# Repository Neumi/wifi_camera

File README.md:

# wifi_camera

### A camera that can see WiFi signals. Just the sensor unit. Currently planned for 8x8=64 pixels.

3D capture of a wifi signal in a 20x20x20 cm grid.

## What it does
The sensor array captures RSSI values from near by WiFi networks and sends the collected pixel data to a master that processes and visualizes the captured data. The goal is to build a sensor, that makes WiFi signal visible in more or less real time.

## Why? 
WiFi signals are invisible to humans. I think it would be fun to make them visible and play around with it. Projects I have in mind unsing the sensor array: real time analysis of antennas and obstacles..., real time object/person detection/tracking by reading WiFi shadows and reflections, using the standing wave to 'surf' it to get position data back for i.e. robots.

## How?
Before this, I built a rig to scan and visualize WiFi signal propagation in 3D 

https://hackaday.com/2021/11/22/visualizing-wifi-with-a-converted-3d-printer/

https://github.com/Neumi/3D_wifi_scanner

This got me interested in building a real time, sensor array to take a whole frame at once without having to scan a slice one position after another.

To capture a whole slice at once, I built this array unsing four PCBs with 4x4 ESP8266 sensor nodes connected via i2c where every pixel is an i2c slave and a master that asks the pixels one by one for the captured values.

I'm currently waiting fore more ESP8266s to arrive.

## Results
The results look pretty granular currently, as I only used 4x4 pixels, which is a bit low. When more ESPs arrive, I will take more images.

16 Pixels, x-axis is time, Y axis is RSSI with an offset between each pixel for visibility.

16 Pixels with correct orientation in a 2D plot. 

## Video of 4x4 test grid:

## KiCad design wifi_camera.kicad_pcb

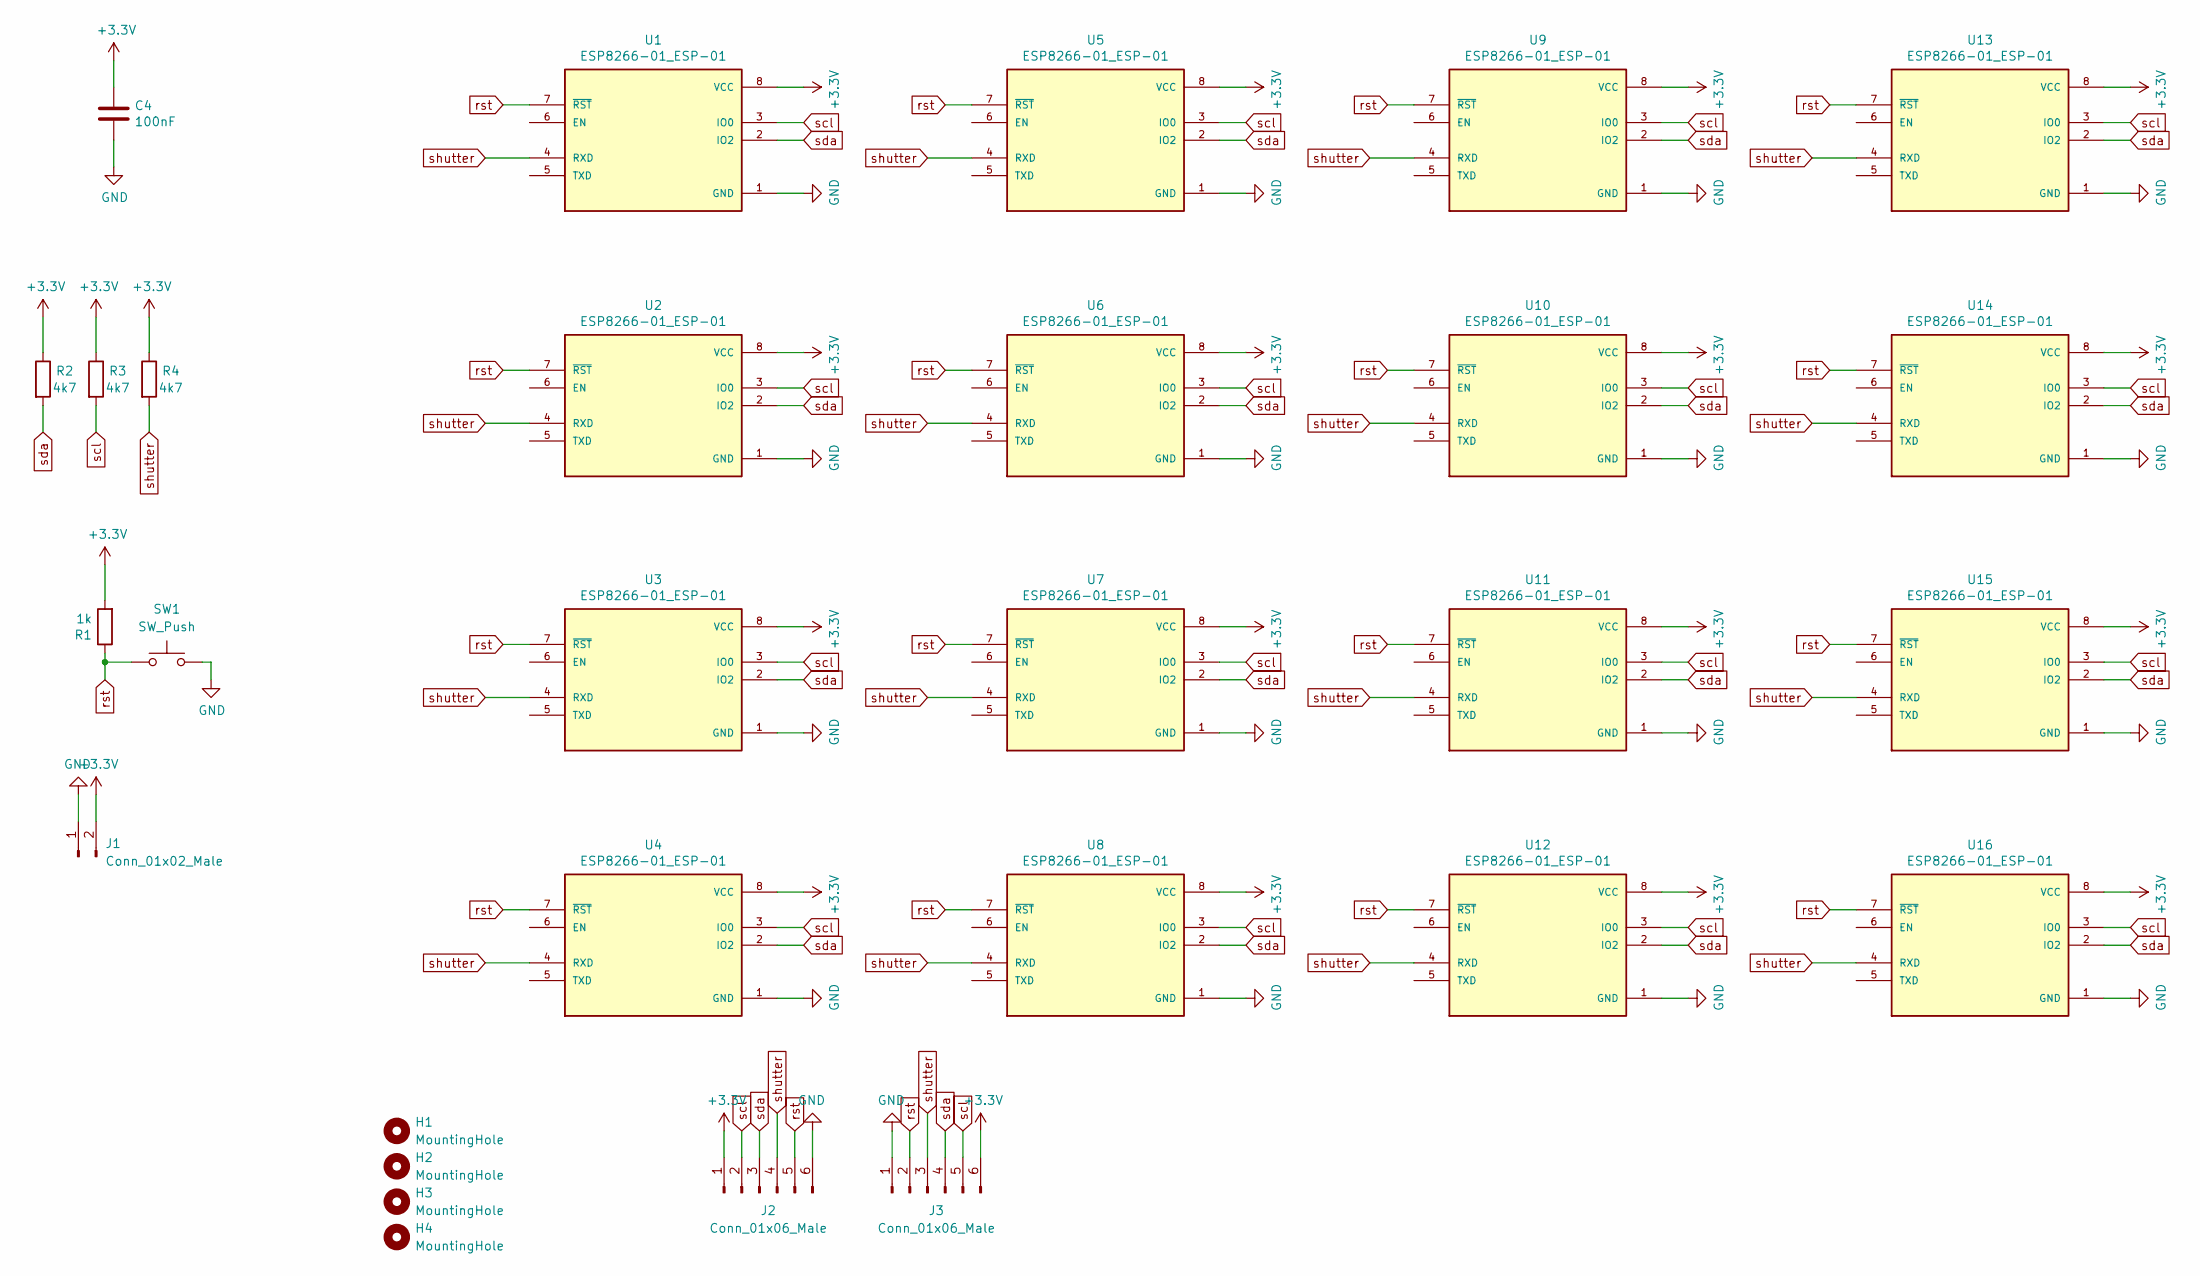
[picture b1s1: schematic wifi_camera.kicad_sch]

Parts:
C4: 100nF; C_0805_2012Metric
H1, H2, H3, H4: MountingHole; MountingHole_3.2mm_M3
J1: Conn_01x02_Male; AMASS_XT30PW-M_1x02_P2.50mm_Horizontal
J2, J3: Conn_01x06_Male; JST_EH_B6B-EH-A_1x06_P2.50mm_Vertical
R1: 1k; R_Axial_DIN0309_L9.0mm_D3.2mm_P12.70mm_Horizontal
R2, R3, R4: 4k7; R_Axial_DIN0309_L9.0mm_D3.2mm_P12.70mm_Horizontal
SW1: SW_Push; SW_PUSH_6mm
U1, U2, U3, U4, U5, U6, U7, U8, U9, U10, U11, U12, U13, U14, U15, U16: ESP8266-01_ESP-01; XCVR_ESP8266-01_ESP-01; PARTREV V1.2

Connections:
+3V3: C4.1, J1.2, J2.1, J3.6, R1.2, R2.1, R3.1, R4.1, U1.8 (VCC), U2.8 (VCC), U3.8 (VCC), U4.8 (VCC), U5.8 (VCC), U6.8 (VCC), U7.8 (VCC), U8.8 (VCC), U9.8 (VCC), U10.8 (VCC), U11.8 (VCC), U12.8 (VCC), U13.8 (VCC), U14.8 (VCC), U15.8 (VCC), U16.8 (VCC)
GND: C4.2, J1.1, J2.6, J3.1, SW1.2, U1.1 (GND), U2.1 (GND), U3.1 (GND), U4.1 (GND), U5.1 (GND), U6.1 (GND), U7.1 (GND), U8.1 (GND), U9.1 (GND), U10.1 (GND), U11.1 (GND), U12.1 (GND), U13.1 (GND), U14.1 (GND), U15.1 (GND), U16.1 (GND)
rst: J2.5, J3.2, R1.1, SW1.1, U1.7 (~RST), U2.7 (~RST), U3.7 (~RST), U4.7 (~RST), U5.7 (~RST), U6.7 (~RST), U7.7 (~RST), U8.7 (~RST), U9.7 (~RST), U10.7 (~RST), U11.7 (~RST), U12.7 (~RST), U13.7 (~RST), U14.7 (~RST), U15.7 (~RST), U16.7 (~RST)
scl: J2.2, J3.5, R3.2, U1.3 (IO0), U2.3 (IO0), U3.3 (IO0), U4.3 (IO0), U5.3 (IO0), U6.3 (IO0), U7.3 (IO0), U8.3 (IO0), U9.3 (IO0), U10.3 (IO0), U11.3 (IO0), U12.3 (IO0), U13.3 (IO0), U14.3 (IO0), U15.3 (IO0), U16.3 (IO0)
sda: J2.3, J3.4, R2.2, U1.2 (IO2), U2.2 (IO2), U3.2 (IO2), U4.2 (IO2), U5.2 (IO2), U6.2 (IO2), U7.2 (IO2), U8.2 (IO2), U9.2 (IO2), U10.2 (IO2), U11.2 (IO2), U12.2 (IO2), U13.2 (IO2), U14.2 (IO2), U15.2 (IO2), U16.2 (IO2)
shutter: J2.4, J3.3, R4.2, U1.4 (RXD), U2.4 (RXD), U3.4 (RXD), U4.4 (RXD), U5.4 (RXD), U6.4 (RXD), U7.4 (RXD), U8.4 (RXD), U9.4 (RXD), U10.4 (RXD), U11.4 (RXD), U12.4 (RXD), U13.4 (RXD), U14.4 (RXD), U15.4 (RXD), U16.4 (RXD)

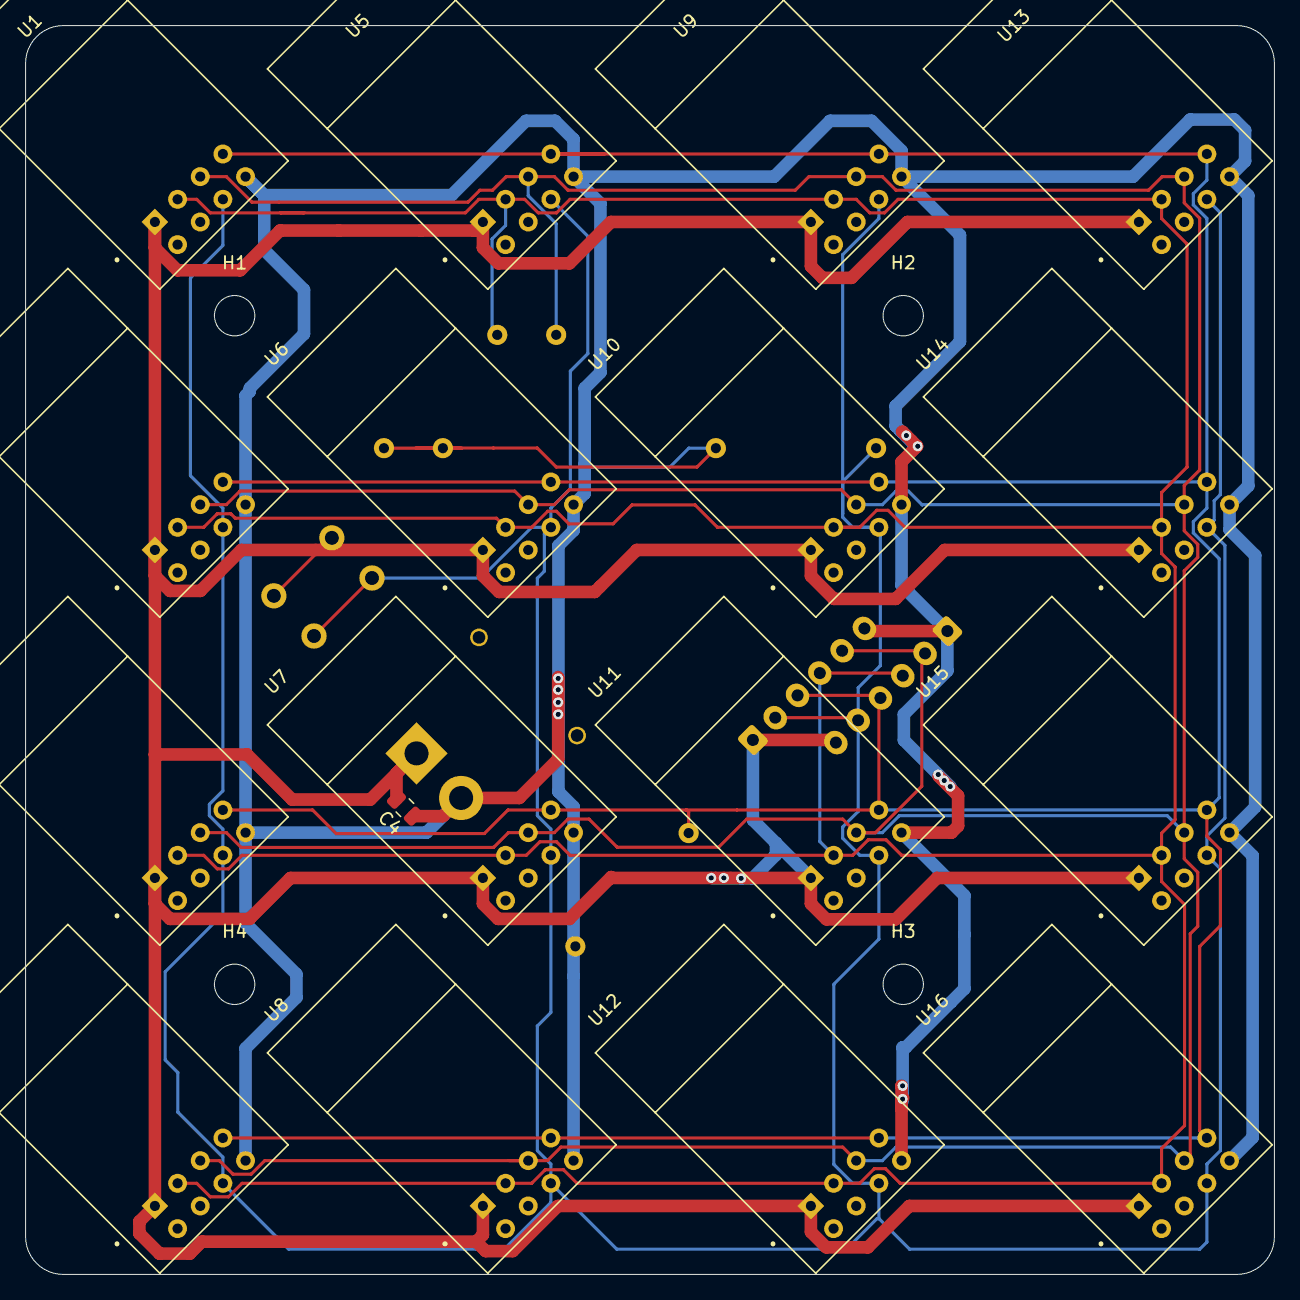
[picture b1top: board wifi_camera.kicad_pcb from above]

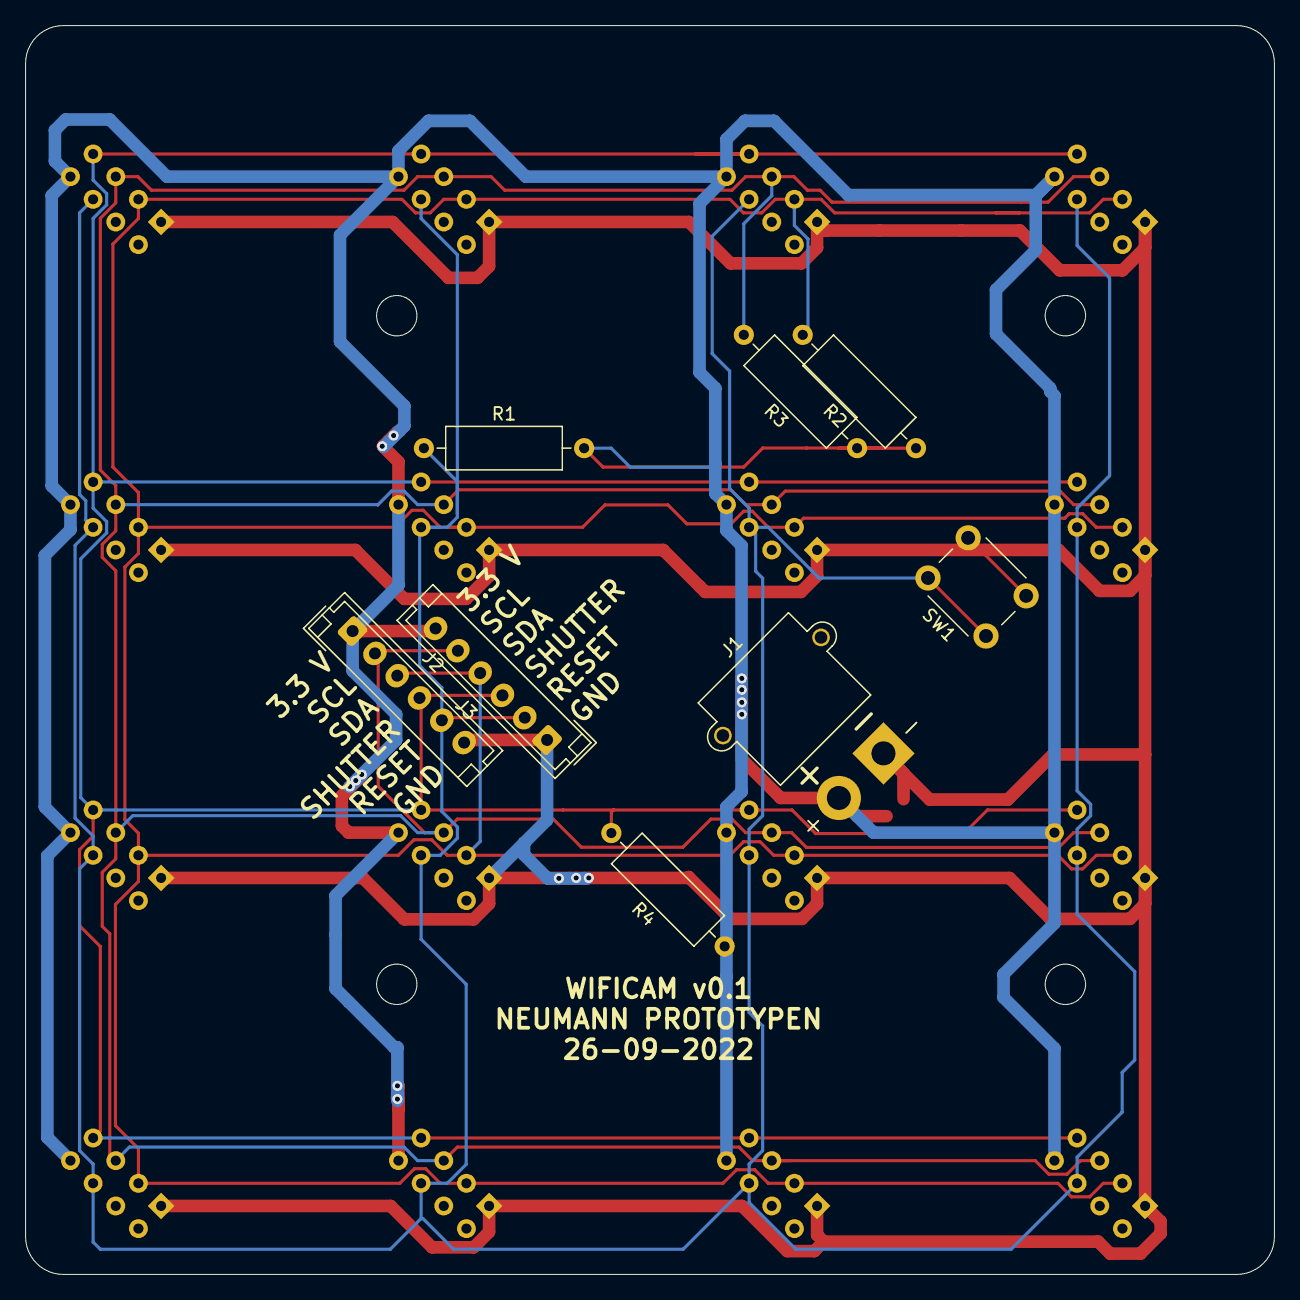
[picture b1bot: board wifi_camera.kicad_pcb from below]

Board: 2 copper layers, 99.0 x 99.0 mm, 29 parts (8 on the bottom side), 6 nets.

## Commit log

2022-10-24 added electroncs, layout, schematics and source code for pixels and master using i2c
2022-10-24 added images
2022-10-24 added python code for visualization, stack processing and real time preview
2022-10-24 removed venv
2022-10-24 cleanup
